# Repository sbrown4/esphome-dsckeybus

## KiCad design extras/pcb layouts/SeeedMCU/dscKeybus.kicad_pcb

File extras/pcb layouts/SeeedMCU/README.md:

# Seeed XIAO-ESP32-S3/C3 based DSC Keybus Interface
## Features
- The mcu modules are in wide distribution and available from reliable sources such as Mouser and Digikey.
- A u.fl antenna connector on the mcu for an external antenna when the device is installed in a metalic DSC enclosure
- Mounting holes and form factor compatible with DSC expansion modules
- MOSFET level converters
- Optional NPN driver for the data line when using the device as a diagnostic tool. Using the same GPIO for both reading and writing data makes it impossible to monitor the bus when writing. NPN driver chosed because library inverts output.
- Fixed 5VDC buck DC-DC converter that can be disconnected when powering via USB
- Serial I/O extended to a header for diagnostic output when device is powered by the Keybus
- Pads for soldering modules with castellated pads. This allows for either headers or direct soldering of the mcu and DC-DC converter
- Thru-hole pads to allow assembly with conventional not SMD soldering skills
## Questions for next version
- TVS diodes on clock and data?
- Extend additonal GPIOs to a header?
- Convert serial I/O header to 6 pins for compatibility with FTDI TTL-232R-3V3 cable.
## Precautions
- Don't power the device without an antenna connected. Regardless of its low power output, there are reports that the power amp gets fried. 
## Parts List
- J1 TE_282837-4 1x4 screw terminal
- J2 1x2 2.54mm vertical pin header
- J3 1x3 2.54mm vertical pin header
- Q2,Q3 2N7000 inline
- Q1 2N3904 inline
- U1 Seeed XIAO ESP32S3 with u.fl antenna connector
- U2 MP1848EN 5V DC-DC buck converter
- R1 1K 1/4W resistor
-    u.fl to RP-SMA cable assembly
-    RP-SMA 2.4GHz antenna
-    Reverse locking support Essentra Components RLCBSR-6-01

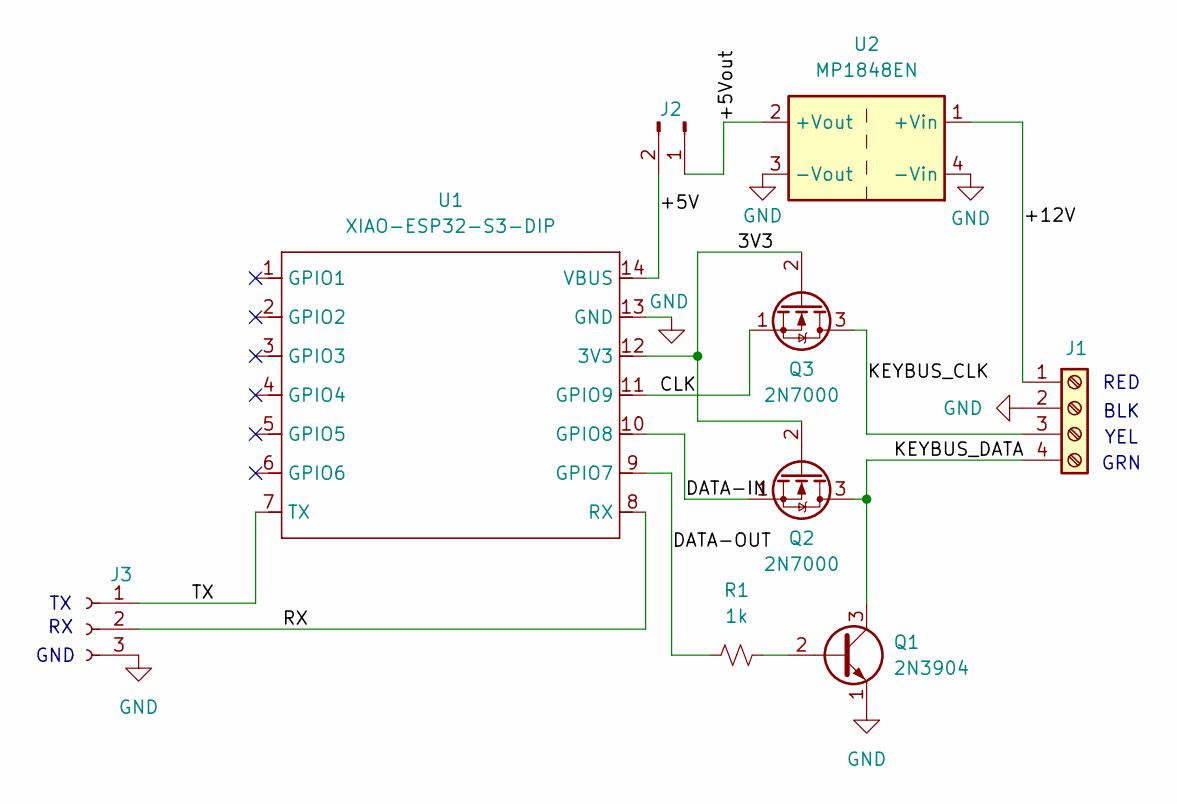
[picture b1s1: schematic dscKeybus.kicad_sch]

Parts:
J1: Screw_Terminal_01x04; TE_282837-4
J2: Conn_01x02_Pin; PinHeader_1x02_P2.54mm_Vertical
J3: Conn_01x03_Socket; PinSocket_1x03_P2.54mm_Vertical
Q1: 2N3904; TO-92_HandSolder
Q2, Q3: 2N7000; TO-92_HandSolder
R1: 1k; R_Axial_DIN0207_L6.3mm_D2.5mm_P7.62mm_Horizontal
U1: XIAO-ESP32-S3-DIP; XIAO-ESP32S3-DIP
U2: MP1848EN; MP1584EN_Power_Module_5VDC

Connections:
/3V3: Q2.2 (G), Q3.2 (G), U1.12 (3V3)
/+5V: J2.2, U1.14 (VBUS)
/+5Vout: J2.1, U2.2 (+Vout)
/+12V: J1.1, U2.1 (+Vin)
/CLK: Q3.1 (S), U1.11 (GPIO9)
/DATA-IN: Q2.1 (S), U1.10 (GPIO8)
/DATA-OUT: R1.2, U1.9 (GPIO7)
/KEYBUS_CLK: J1.3, Q3.3 (D)
/KEYBUS_DATA: J1.4, Q1.3 (C), Q2.3 (D)
/RX: J3.2, U1.8 (RX)
/TX: J3.1, U1.7 (TX)
GND: J1.2, J3.3, Q1.1 (E), U1.13 (GND), U2.3 (-Vout), U2.4 (-Vin)
unnamed: Q1.2 (B), R1.1

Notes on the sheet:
RED
GRN
YEL
GND
BLK

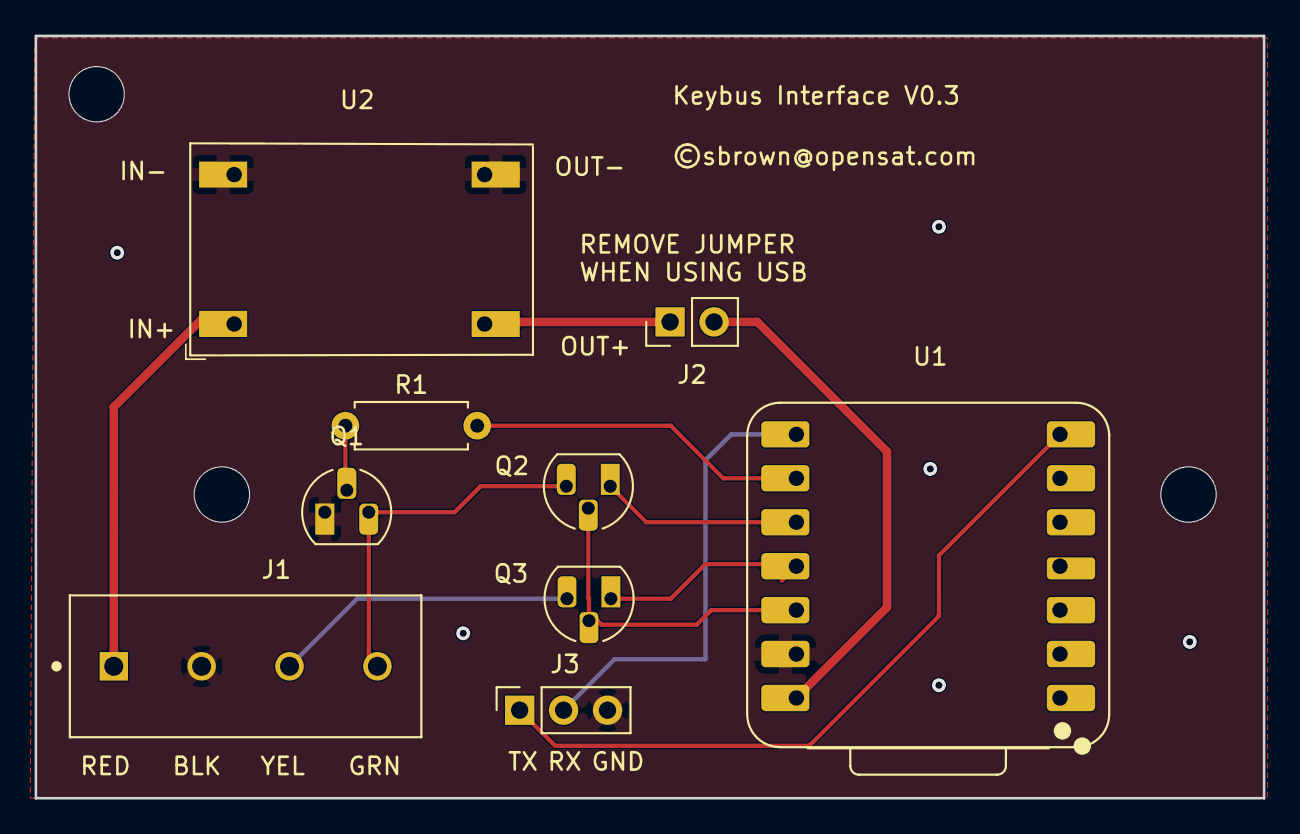
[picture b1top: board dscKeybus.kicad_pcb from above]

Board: 2 copper layers, 71.0 x 44.1 mm, 9 parts (0 on the bottom side), 13 nets.

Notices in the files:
extras/pcb layouts/SeeedMCU/dscKeybus.kicad_pcb:
©sbrown@opensat.com
